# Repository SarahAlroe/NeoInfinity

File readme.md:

# NeoInfinity animated neopixel infinity symbol

KiCad board files and Arduino code for building a little animated infinity symbol. Makes use of [
Spence Kondes megaTinyCore](https://github.com/SpenceKonde/megaTinyCore) Arduino core and libraries for driving 27 NeoPixels with an ATtiny412. Can run from a 5V source or battery power. Implements temporal error diffusion to obtain lower brightness levels while maintaining reasonable color detail.

## Assembly

A stencil is not necessary but recommended for the top layer.

Components:
- 17 x 100nF 0603 capacitors. Most if not all can probably be skipped without issue.
- 1 x 10µF 0603 capacitor.
- 27 x WS2812B 5x5mm Addressable RGB LEDs.
- 1 x ATtiny412 SOIC package.
- 1 x EVQP2 push button.
- 1 x 3 pin SMD 2.54mm socket
- 1 x JST PH SMD connector (JST_S2B-PH-SM4-TB)

[Interactive BOM](http://htmlpreview.github.io/?https://github.com/SarahAlroe/NeoInfinity/blob/main/bom/ibom.html)

## Software

Only dependent on the [megaTinyCore](https://github.com/SpenceKonde/megaTinyCore/blob/master/Installation.md) and its libraries.  
Some notes:
- Try to stick with a 20MHz clock speed or as high as voltage allows for nicer persistence of vision. Animations speed is kept consistent across clock speeds.
- Disable milis() and use minimal printf() option to make code fit. Current compile lands at ~95% flash.

## Extras

- PatternPositions - Calculations of where each neopixel is along various directions. 
- StencilCase - SVG and FreeCad model for holding PCBs and a 120x120mm stencil positioned.  
- Without QR block - Version of the PCB layout without the 8x8mm square on the back replaced with a unique qr code on production.

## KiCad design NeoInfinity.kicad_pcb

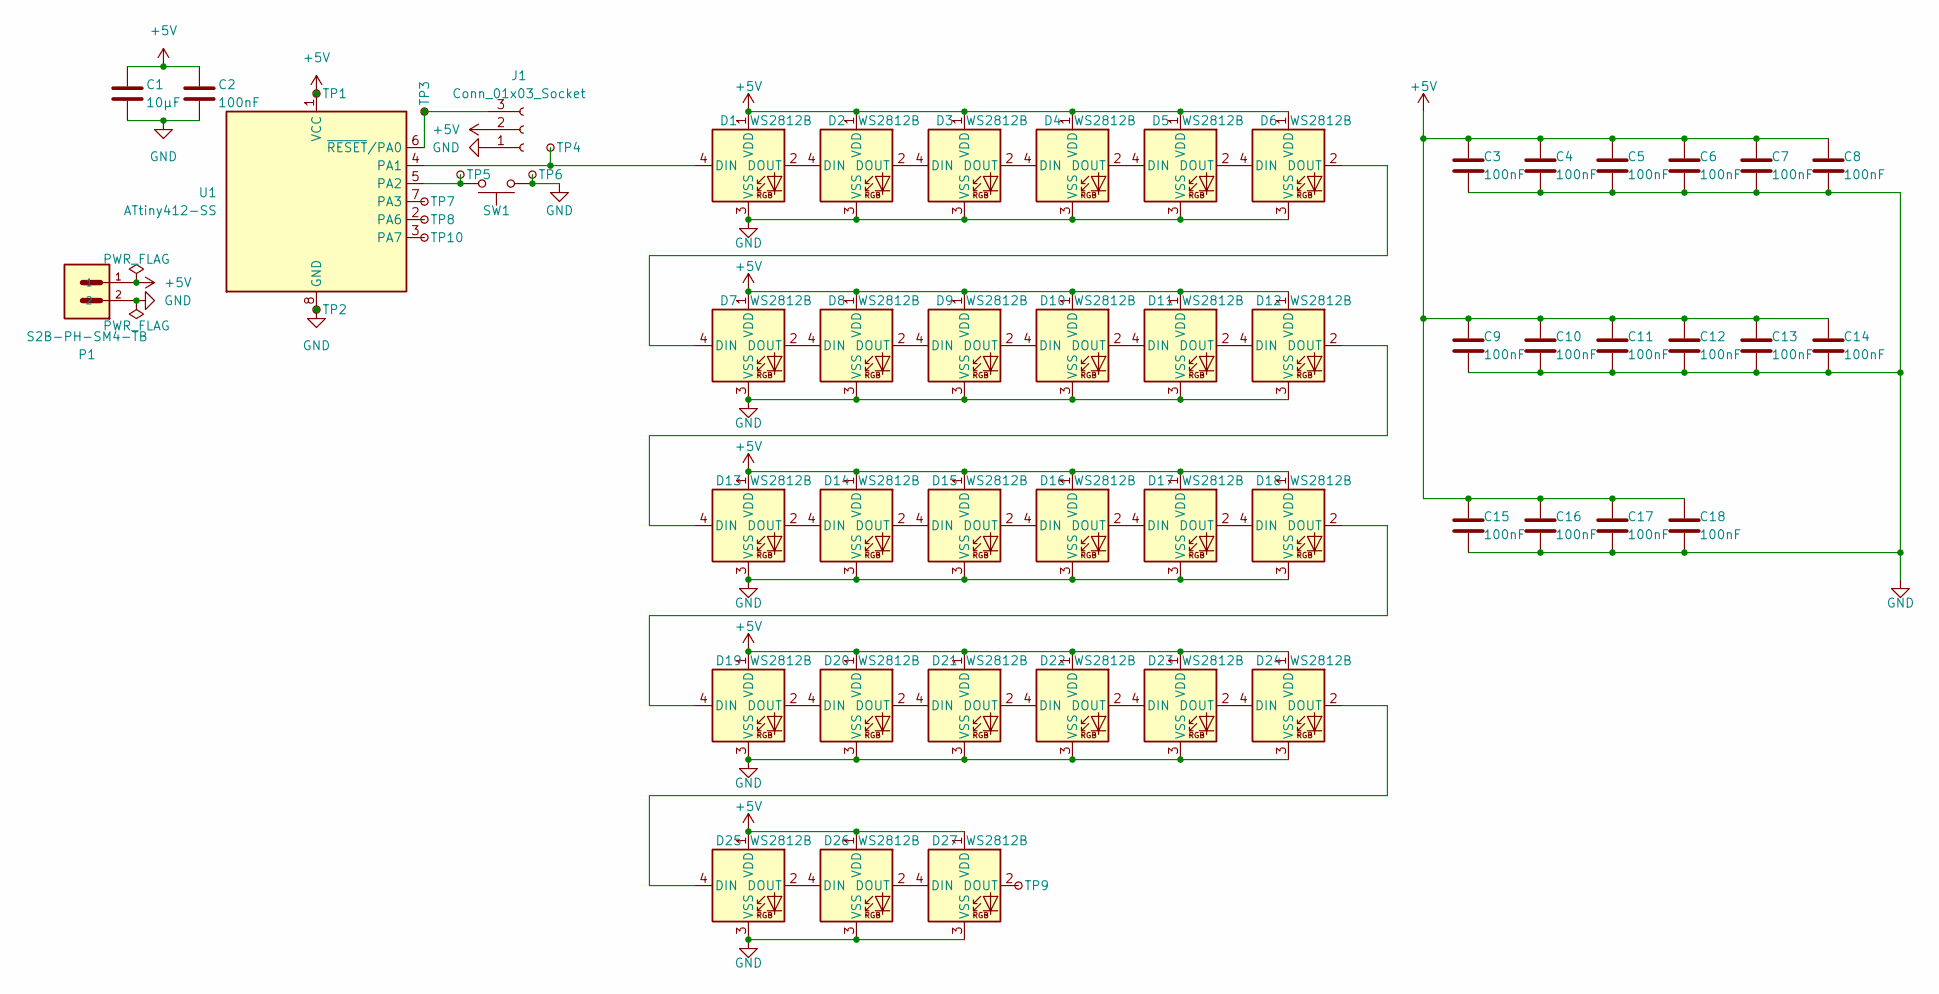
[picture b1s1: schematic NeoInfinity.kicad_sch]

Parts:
C1: 10µF; C_0603_1608Metric
C2, C3, C4, C5, C6, C7, C8, C9, C10, C11, C12, C13, C14, C15, C16, C17, C18: 100nF; C_0603_1608Metric
D1, D2, D3, D4, D5, D6, D7, D8, D9, D10, D11, D12, D13, D14, D15, D16, D17, D18, D19, D20, D21, D22, D23, D24, D25, D26, D27: WS2812B; LED_WS2812B_PLCC4_5.0x5.0mm_P3.2mm
J1: Conn_01x03_Socket; GCT_BG300-03-X-X-A_REVC
P1: S2B-PH-SM4-TB; JST_S2B-PH-SM4-TB
SW1: SW_Push; SW_SPST_EVQP2
TP1, TP2, TP3, TP4, TP5, TP6, TP7, TP8, TP9, TP10: TestPoint_Small; TestPoint_Pad_D2.0mm
U1: ATtiny412-SS; SOIC-8_3.9x4.9mm_P1.27mm

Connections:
+5V: C1.1, C2.1, C3.1, C4.1, C5.1, C6.1, C7.1, C8.1, C9.1, C10.1, C11.1, C12.1, C13.1, C14.1, C15.1, C16.1, C17.1, C18.1, D1.1 (VDD), D2.1 (VDD), D3.1 (VDD), D4.1 (VDD), D5.1 (VDD), D6.1 (VDD), D7.1 (VDD), D8.1 (VDD), D9.1 (VDD), D10.1 (VDD), D11.1 (VDD), D12.1 (VDD), D13.1 (VDD), D14.1 (VDD), D15.1 (VDD), D16.1 (VDD), D17.1 (VDD), D18.1 (VDD), D19.1 (VDD), D20.1 (VDD), D21.1 (VDD), D22.1 (VDD), D23.1 (VDD), D24.1 (VDD), D25.1 (VDD), D26.1 (VDD), D27.1 (VDD), J1.2, P1.1, TP1.1, U1.1 (VCC)
GND: C1.2, C2.2, C3.2, C4.2, C5.2, C6.2, C7.2, C8.2, C9.2, C10.2, C11.2, C12.2, C13.2, C14.2, C15.2, C16.2, C17.2, C18.2, D1.3 (VSS), D2.3 (VSS), D3.3 (VSS), D4.3 (VSS), D5.3 (VSS), D6.3 (VSS), D7.3 (VSS), D8.3 (VSS), D9.3 (VSS), D10.3 (VSS), D11.3 (VSS), D12.3 (VSS), D13.3 (VSS), D14.3 (VSS), D15.3 (VSS), D16.3 (VSS), D17.3 (VSS), D18.3 (VSS), D19.3 (VSS), D20.3 (VSS), D21.3 (VSS), D22.3 (VSS), D23.3 (VSS), D24.3 (VSS), D25.3 (VSS), D26.3 (VSS), D27.3 (VSS), J1.1, P1.2, SW1.2, TP2.1, TP6.1, U1.8 (GND)
unnamed: D1.4 (DIN), TP4.1, U1.4 (PA1)
unnamed: D1.2 (DOUT), D2.4 (DIN)
unnamed: D2.2 (DOUT), D3.4 (DIN)
unnamed: D3.2 (DOUT), D4.4 (DIN)
unnamed: D4.2 (DOUT), D5.4 (DIN)
unnamed: D5.2 (DOUT), D6.4 (DIN)
unnamed: D6.2 (DOUT), D7.4 (DIN)
unnamed: D7.2 (DOUT), D8.4 (DIN)
unnamed: D8.2 (DOUT), D9.4 (DIN)
unnamed: D9.2 (DOUT), D10.4 (DIN)
unnamed: D10.2 (DOUT), D11.4 (DIN)
unnamed: D11.2 (DOUT), D12.4 (DIN)
unnamed: D12.2 (DOUT), D13.4 (DIN)
unnamed: D13.2 (DOUT), D14.4 (DIN)
unnamed: D14.2 (DOUT), D15.4 (DIN)
unnamed: D15.2 (DOUT), D16.4 (DIN)
unnamed: D16.2 (DOUT), D17.4 (DIN)
unnamed: D17.2 (DOUT), D18.4 (DIN)
unnamed: D18.2 (DOUT), D19.4 (DIN)
unnamed: D19.2 (DOUT), D20.4 (DIN)
unnamed: D20.2 (DOUT), D21.4 (DIN)
unnamed: D21.2 (DOUT), D22.4 (DIN)
unnamed: D22.2 (DOUT), D23.4 (DIN)
unnamed: D23.2 (DOUT), D24.4 (DIN)
unnamed: D24.2 (DOUT), D25.4 (DIN)
unnamed: D25.2 (DOUT), D26.4 (DIN)
unnamed: D26.2 (DOUT), D27.4 (DIN)
unnamed: D27.2 (DOUT), TP9.1
unnamed: J1.3, TP3.1, U1.6 (~RESET/PA0)
unnamed: SW1.1, TP5.1, U1.5 (PA2)
unnamed: TP7.1, U1.7 (PA3)
unnamed: TP8.1, U1.2 (PA6)
unnamed: TP10.1, U1.3 (PA7)

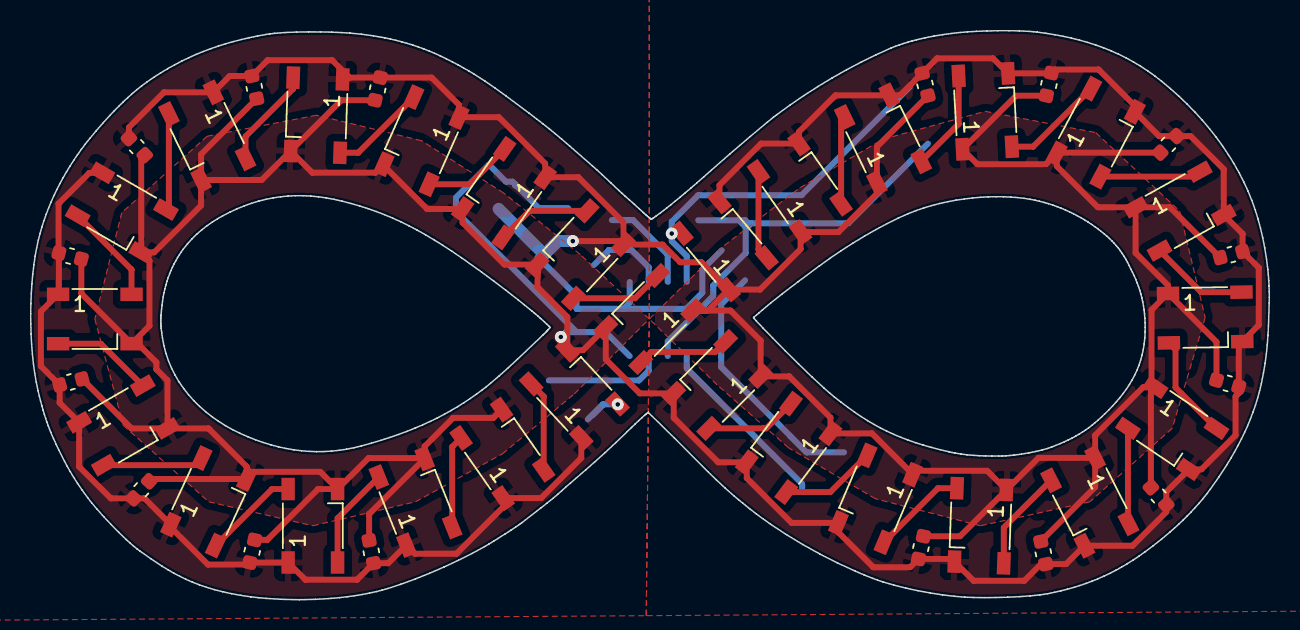
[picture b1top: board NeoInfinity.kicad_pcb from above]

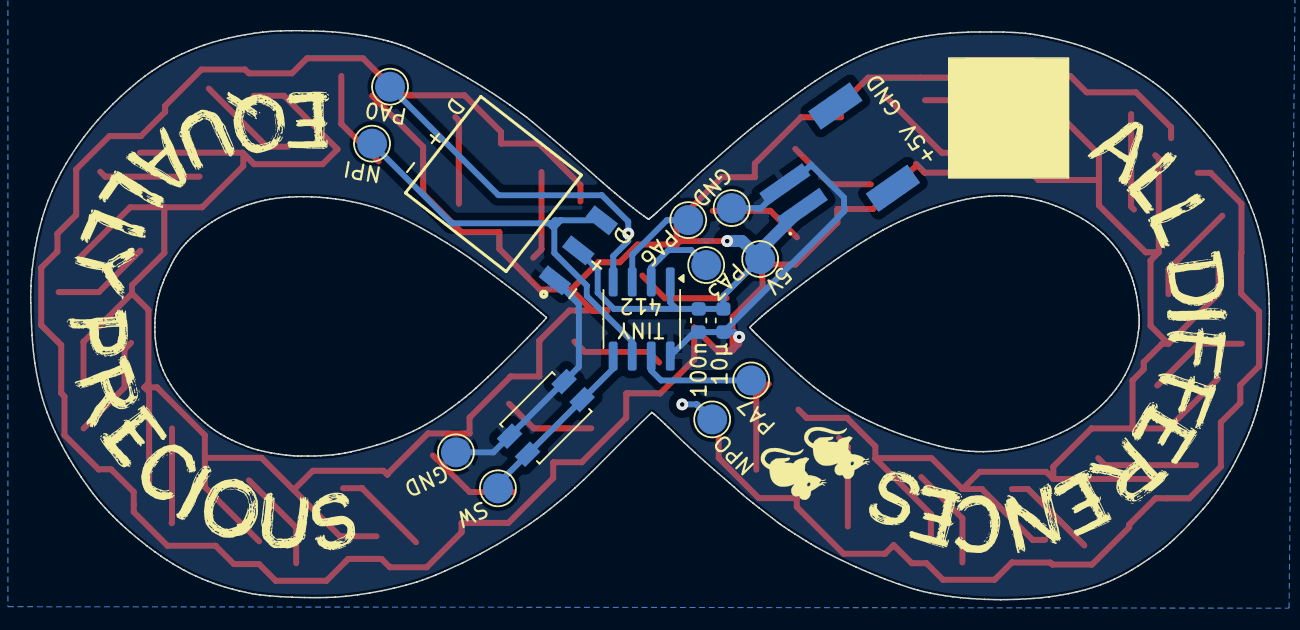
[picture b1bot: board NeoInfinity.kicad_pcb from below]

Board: 2 copper layers, 82.7 x 38.0 mm, 59 parts (16 on the bottom side), 35 nets.

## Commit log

2025-02-09 Init
2025-02-09 Added interactive BOM
2025-03-01 Switched to ordered dithering
